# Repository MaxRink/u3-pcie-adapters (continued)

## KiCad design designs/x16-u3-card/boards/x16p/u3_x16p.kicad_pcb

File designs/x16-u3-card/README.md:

# U.3 adapter boards: x16 card, x8 card, OCuLink cage board

Passive PCIe 4.0 boards that carry true SFF-TA-1001 (U.3) wiring to 2.5" U.3 drives such as the
HPE P50230-B21 / Samsung PM1735a, which refuse U.2-wired hosts. Designed for a Jonsbo N5 build
with a 3D-printed cooling shroud.

## Boards

| Board | What it is | Status |
| --- | --- | --- |
| **x8 card** (`boards/x8/`) | x8 slot (x4x4 bifurcation), 2 drives standing upright on their connectors, connectors facing the motherboard, passive, REFCLK buffer, full sidebands, per-drive 12 V jumper and eFuse, 190 mm | rev F routed, DRC clean, all lanes ≤50 mm |
| **x16 card, passive, 4 drives** (`boards/x16p/`) | x16 slot (x4x4x4x4), 4 upright drives in a row on a 312 mm card; drives B–D sit 5.7 mm higher so lanes 8–15 pass under drive B | rev F; drive A in budget, B 45–54 mm, C ~110 mm, D ~170 mm: C/D run at PCIe Gen3 (silk says so), Gen4 on all four comes with the retimer card |
| **x16 card, passive, 3 drives** (`boards/x16p3/`) | same card with drives A–C only, 239 mm; host bifurcation x4x4x4 or x8x4x4, lanes 12–15 unused | rev F; drive C at PCIe Gen3 |
| **CDCDB400 clock versions** (`boards/*-cdcdb400/`) | the three cards above with a TI CDCDB400 instead of the PI6CB33401 / 9DBL0442 buffer | see [`docs/part-options.md`](../../docs/part-options.md) |
| **x16 card with retimer** | as above, with a retimer on lanes 8–15 so all 4 drives stay compliant | planned (part search) |
| **OCuLink cage board** (`boards/cage/`) | OCuLink 4i (SFF-8611) to U.3 breakout for a drive in a printed cage; 12 V in on a PCIe 6-pin | rev B routed, DRC clean (review fixes applied; the cabled path still needs a host-card retimer for full compliance) |

Renders are regenerated from the KiCad files whenever a board changes (see
[`tools/render`](../../tools/render/)); boards still in layout get their renders when they are DRC clean.

## OCuLink cage board

Rev B. 56.5 x 37.65 mm, 6 layers (JLC06161H-3313), PCIe lanes on L1/L6 only. The OCuLink receptacle sits on the
bottom in the edge notch, the U.3 receptacle on top mates the drive at the upper edge, and a PCIe 6-pin
(Molex Mini-Fit Jr) brings 12 V through a 3 A PTC fuse; a SOT-89 LDO (MCP1703AT-3302E/MB, pinout checked
against the Microchip datasheet; the HT7533-1 is an LCSC alternative only after its pinout is checked) makes 3.3 V aux. Four M3 slots (3.2 x 6.2 mm, along the insertion axis) hold it in
the printed cage.

Rev B changes (from the rev A review, `docs/reviews/cage-board-review.md`, and `docs/reviews/full-review-2026-11-13.md`):

- 220 nF AC caps on PER0/PER1 (bottom side, L5 voided under the pads). A U.3 drive has no TX caps on lanes 0/1
  (SFF-TA-1001 Rev 1.1 section 4.5), so rev A left those two lanes DC-coupled.
- The drive-side board edge now ends 9.4 mm from the peg line, 0.65 mm short of the housing face, so the board can
  no longer stop the drive before it is fully seated. The receptacle overhangs the edge by design.
- 100 k pull-down on PERST#: a missing or sideband-less cable holds the drive in reset.
- The four low-speed OCuLink vias moved off the PET via row into two rows in front of it, and a return via was
  added between the PET3 and PET2 transitions. The 11 mm slot in the L2/L5 planes is now two short ones with a
  2.7 mm bridge.
- Parts: F1 mSMD300-16V (3 A hold, C6851473), LED KT-0603YG (C2289), C3 50 V (C307331), LDO as above (the AMS1117
  was at its 15 V limit, needs a minimum load and is not stable with ceramic output caps).

The renders below still show rev A.

Still open on this board: the cabled path needs a retimer on the host card for full PCIe 4.0 compliance
(design-rules Rev E), PERST#/REFCLK/SMBus are not isolated when the cage is unpowered, and the PET0 lane is 30.4 mm
(0.4 mm over the per-board target).

| Top | Bottom (seen from below) |
| --- | --- |
|  |  |
|  |  |

With a 15 mm U.3 drive plugged in:

| Front | Back |
| --- | --- |
|  |  |

Copper, mask and silkscreen in the renders come from the real layer geometry. The U.3 and
OCuLink receptacles, the Mini-Fit header and the drive are simplified appearance models.

Fab files: [`fab/cage/`](fab/cage/) (Gerbers, BOM, CPL for JLCPCB / PCBWay).

## x8 card

CEM x8 edge (bifurcate the slot x4x4). Both U.3 receptacles sit on the bottom, mirrored, so the drives stand
upright with their connectors facing the motherboard and lane order needs no crossings. The card is cut away
behind the drives for airflow. A 9DBL0442 buffer (bottom side, left of the fingers) fans REFCLK out to both drives.
AC caps (220 nF) sit on the drive-to-host lanes per SFF-TA-1001. 190 mm long. Sidebands and 12 V work as described
under [Sidebands and power](#sidebands-and-power). Fab files: [`fab/x8/`](fab/x8/).

## x16 card (passive)

Same construction as the x8, four drives in a row (A–D, 73 mm pitch, 312 mm = CEM full length). The 3-drive card
(`U3_DRIVES=3 python3 gen/x16.py`) is the same design cut after drive C (239 mm). Drive B's
lane pads sit right above fingers 8–15, and right of the fingers the card edge rises to 12.75 mm, so lanes 8–15
run in a 0.9 mm-pitch stack under drive B and drives B–D sit 5.7 mm higher than A to make room. Lane lengths
finger→receptacle: A 30–46 mm, B 45–54 mm, C 107–115 mm, D 164–172 mm (the DRU documents the over-budget nets).
Drives C and D are past the Gen4 loss budget, so they are meant to run at PCIe Gen3 (silk: "C/D: PCIe Gen3 only"); the
retimer card is the Gen4 option for all four.

REFCLK (rev C): the card's 9DBL0442 (same buffer and card-level parts as the x8) feeds drive A directly and starts a
chain on L6 in the channel under drive A's block. Left of drive B a second 9DBL0442 (U40) takes the chain, drives B and
passes the clock on to a third one left of drive C (U41), which drives C and D. On the 3-drive card U40 drives B and C.
So only one clock pair ever runs under a sideband block, every pair stays short between buffers, and each repeater
gets 3.3 V aux from an extra tap on the L3 trunk. The 6-pin aux connector (J5) sits at the card end below drive D's
(or C's) power parts, with its 22 µF bulk cap on the bottom next to the +12 V pins. Fab files: [`fab/x16p/`](fab/x16p/), [`fab/x16p3/`](fab/x16p3/).

## Rev E and rev F changes (x8 and x16 cards)

**Which side the drives are on.** On these cards the receptacles are soldered to the solder side (KiCad bottom), so
the drives hang behind the card, where a CEM card may only be 2.67 mm tall and where the neighbouring slot is. This
was chosen because the U.3 lane order then matches the finger order without crossings. A version with the drives and
all tall parts on the component side is under discussion; it needs a new card-level layout and PCIe lane reversal.

Rev E (from the 2026-11-13 review):

- REFCLK buffer is the Diodes PI6CB33401ZHIEX (pin-identical to the 9DBL0442, which is the BOM alternate). Pin 1 is
  open on every buffer that runs in bypass mode.
- 4-drive card: the last repeater (U41, feeding C and D) runs as a zero-delay buffer (pin 1 to GND, low-bandwidth
  PLL) with its own ferrite and 100 nF on VDDA, so no drive sees more than two buffer delays. **This is only valid
  while drives C and D run at Gen3**, which they do on the passive card.
- TPS2116: slot 3.3 V has priority, 3.3 V aux is the fallback.
- eFuse: ITIMER 4.7 nF (about 2 ms blanking), ILIM 390 Ω (3.85 A), IMON 1 kΩ (0.25 V/A).
- x16 cards: the window edge is 9.9 mm from the receptacle peg line (rev D: 9.4). 9.4 and 9.6 do not route on the
  4-drive card. The housing face is at 10.05 mm, so only 0.15 mm is left. **Fit a drive into a bare board before
  assembling anything** and file the edge back if the drive body touches it.
  When ordering, add the note "window edges +0/-0.2 mm toward the drive": the fab's outline tolerance (about
  0.2 mm) is larger than the 0.15 mm that is left.

Rev F (all parts on the top side, 0603 or larger, or leaded):

| Feature | Where | Notes |
| --- | --- | --- |
| I2C header J6 (1x4, 2.54 mm) | bracket column | 3V3 aux, SCL, SDA, GND of the card-local bus (behind the TCA9548A) |
| EEPROM AT24C02 at 0x50 | bracket column | on the card-local bus, write-enabled |
| Test pads, 1 mm | per drive: 12 V after the eFuse, PG, IMON. Per card: 3V3 aux, 3V3, PERST#, 12 V, 12 V aux, fan tach, fan PWM | last drive's pads are labelled V, P, I |
| GND loops | bracket column and end column | for a scope ground |
| LEDs | per drive: 12 V present after the eFuse. Per card: 12 V, 12 V aux, 3V3 | the per-drive LED hangs on the drive's 12 V (2.2 k), not on PG |
| Fan header J7 (4-pin PWM) | far end of the strip | SJ4 = slot 12 V, SJ5 = aux 12 V, close exactly one. x8: slot is bridged from the fab (one via, about 1 A). x16: aux is bridged (1.0 mm on the top layer from J5, about 3 A). PWM and tach go to test pads only, so a 4-wire fan runs at full speed. **A fan above about 1 A (any 92x38 server fan) must run from aux: cut SJ4 and close SJ5 on the x8**, it does not fit the 66 W slot budget next to the drives either |
| TVS SMBJ15A | at J5 | on 12 V aux |
| M3 holes | H7–H10 in the two columns, H11 up in the strip between drives | the strip holes are searched after routing; a gap without a free spot gets none (x16: the gap between B and C on the 4-drive card) |
| Silk | bracket column | I2C address table and jumper legend |

## Sidebands and power

Every drive has its own sideband block next to its receptacle (`gen/sideband.py`), all on 3.3 V aux:

| Part | Address | Does |
| --- | --- | --- |
| TCA9543A SMBus switch | 0x70 + drive index | slot SMBus (B5/B6) to the drive's SMBus on channel 0, so drives with the same address don't collide |
| TCA9554 IO expander | 0x20 + drive index | P0 PWRDIS (10k pull-down: drive on by default), P1 DualPortEn#, P2 reset enable (pull-up), P3 locate LED, P4 PRSNT#, P5 IfDet#, P6 IfDet2#, P7 WAKE# (inputs pulled up) |
| 74LVC1G11 | | PERST0#/PERST1# = slot PERST# AND reset enable AND the drive's eFuse power-good: a drive stays in reset until its own 12 V is up, and software can hold one drive in reset |
| 74LVC1G07 | | drive WAKE# to slot WAKE# (B11), open drain, wired-OR across drives |

Card-level parts (rev C, `gen/cardkit.py`, left of the fingers):

| Part | Does |
| --- | --- |
| TCA9548A SMBus switch, 0x77 | slot SMBus to a card-local bus on channel 0, so the drive-side switches and expanders (0x70+, 0x20+) never sit on the host's segment. Close SJ1–SJ3 to move it to 0x70–0x76 if the host already uses 0x77 |
| TPS2116 power mux | card 3.3 V aux rail = slot 3.3 V (priority, rev E) or slot 3.3Vaux when main 3.3 V is off, so in S0 the card never loads 3.3Vaux |
| PI6CB33401 REFCLK buffer (9DBL0442 pinout) | slot REFCLK to every drive; its own 3.3 V through a ferrite |

HPT0 (S15) is tied to GND for U.3 x4. REFCLK1 and port B stay open (single-port x4). CLKREQ# (B12) is tied low, so
the host always drives REFCLK (as on cards without clock power management). WAKE# from every drive reaches the slot
through its 74LVC1G07 and can also be read on its expander. SMBus, 3.3 V aux, PERST# and WAKE# run as trunks on L3,
with one tap via per drive block.

**12 V:** each drive has a 3-pin jumper (JP1–JP4). Shunt on pins 2–3 (default) = slot 12 V, pins 1–2 = the PCIe
6-pin (J5). One shunt can never join the two supplies. L4 is split into a slot-12 V plane next to the fingers and an
aux-12 V plane fed only by J5. A slot gives at most 66 W at 12 V, so with more than two 25 W drives move some jumpers
to aux and plug in the 6-pin. Jumper shunts (2.54 mm) are not in the BOM. After the jumper each drive has a
TPS25982 eFuse (3.85 A circuit breaker with about 2 ms blanking, soft start, latch-off on a fault) feeding the drive's 12 V pins and bulk
caps; its power-good holds that drive's PERST#.

**Rules beyond the shared design rules (in each board's DRU):**
- Sideband blocks route at 0.127 mm tracks and 0.15 mm clearance (fab minimum 0.1 / 0.1).
- x16: REFCLK repeater links (REFCLK_R*, B, C, D) may have up to 12 mm uncoupled length (two via fans, two QFN pin
  fan-outs and the skew bumps for the turns); the other REFCLK pairs keep 8 mm.
- The eFuse's 0.5 mm-pitch QFN pins fan out at 0.2 mm on the 12 V nets inside the EFUSE rule areas; the pours carry the current.
- The slot REFCLK input may run up to 16 mm uncoupled (P/N swap at the buffer plus its deskew bumps). REFCLK is 100 MHz, so this costs no margin.
- The card's resistor array is RN10, so it does not clash with the drive blocks' RN1–RN4.

## Cooling

The drives sit in a row along the card, so the shroud's air passes them one after the other and
the last one runs hottest. Summary from [`docs/thermal`](../../docs/thermal/) (25 W per drive, 35 °C
air in, 70 °C case limit, 5 mm between drive and shroud wall):

- **x8, 2 drives:** ~20 CFM. A 92x38 mm server-class fan (~150 Pa) gives ~29 CFM and ~66 °C.
- **x16, 4 drives:** ~30 CFM at ~150 Pa. A 92x38 server fan only reaches ~28 CFM, so ~71 °C:
  marginal. 3 mm gaps (~68 °C) or a 20 W drive power state (~64 °C) give margin.
- 92x25 mm fans don't have the pressure for either card. Close the 3 mm slots between the drives
  in the shroud; they only hold stagnant air.

| CFD, 2 drives in line | CFD, 4 drives in line |
| --- | --- |
|  |  |

## Renders: x8 and x16 cards

Rendered from the routed boards in `boards/x8/` and `boards/x16p/` (PR #8), with 15 mm drives plugged in.

| x8 card | x16 card (passive) |
| --- | --- |
|  |  |
|  |  |
|  |  |
|  |  |

## Generator

All boards are generated by Python scripts on KiCad 7 `pcbnew`. To change a board, edit its script and rerun it; don't hand-edit the board.

- `lib/`: custom footprints (Amphenol PSAS4F213002 U.3 receptacle, Amphenol G14A421211112HR OCuLink 4i) and symbols
- `gen/pcbkit.py`: layout toolkit (pair router with skew bumps, zones, rule areas, DRC)
- `gen/x8.py`: x8 card (2 upright drives on the bottom, REFCLK fan-out buffer, drive window for airflow)
- `gen/x16.py`: x16 passive card (4 drives; `U3_DRIVES=3` for the 3-drive card)
- `gen/sideband.py`: per-drive sideband block (SMBus switch, IO expander, PERST# and WAKE# gates, 12 V jumper, eFuse)
- `gen/cardkit.py`: card-level parts shared by the x8 and x16 cards (REFCLK buffer, SMBus switch, 3.3 V aux OR, trunks)
- `gen/extras.py`: rev F additions (headers, test pads, LEDs, fan header, holes); runs after the block routing
- Switches: `U3_DRIVES=3|4`, `U3_CLK=cdcdb400` (alternate clock buffer, own `boards/*-cdcdb400` folder), `STAGE=card` (quick build without block routing)
- `gen/router.py`: grid maze router for the low-speed sideband nets, with rip-up and reroute and a connectivity check at the end
- `gen/cage.py`: Design 3, the OCuLink 4i to U.3 cage board (rev B, DRC clean)
- `gen/fab.py`: Gerbers, drill, BOM and CPL (JLCPCB/PCBWay)
- `boards/<board>/`: generated KiCad project, DRC report, per-net lengths
- `fab/<board>/`: Gerber zip, BOM and CPL for ordering
- `docs/ref/`: vendor drawings and third-party licences

Rules come from `../../design-rules/` (copied into each board at generation time).

Run: `python3 gen/fplib.py && python3 gen/symlib.py && python3 gen/cage.py && python3 gen/fab.py boards/cage/u3_cage.kicad_pcb boards/cage/bom_raw.json fab/cage`

Render: `xvfb-run -a python3 ../../tools/render/render.py boards/cage/u3_cage.kicad_pcb ../../docs/img/x16-u3-card --prefix cage --drives`

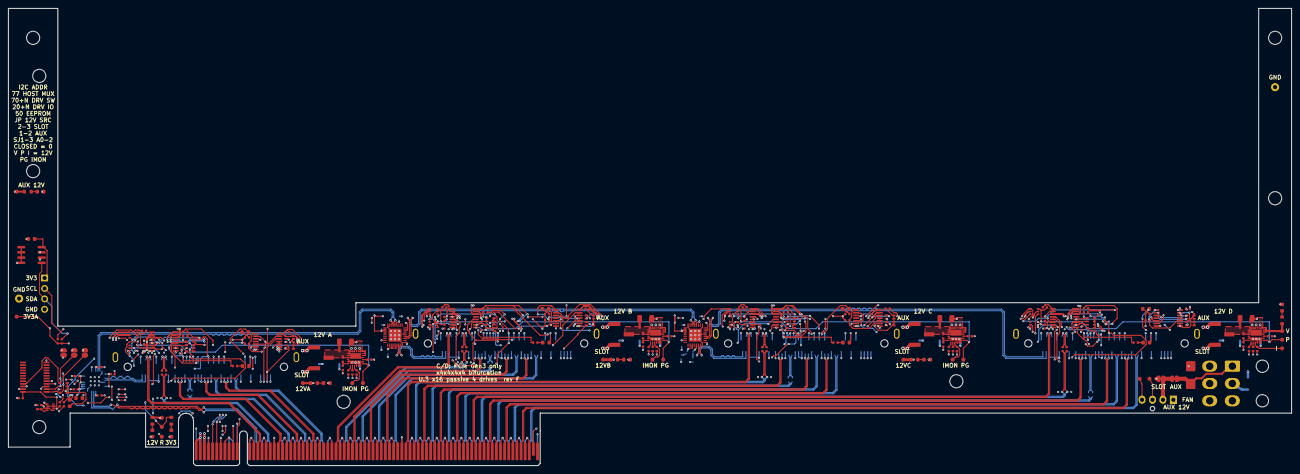
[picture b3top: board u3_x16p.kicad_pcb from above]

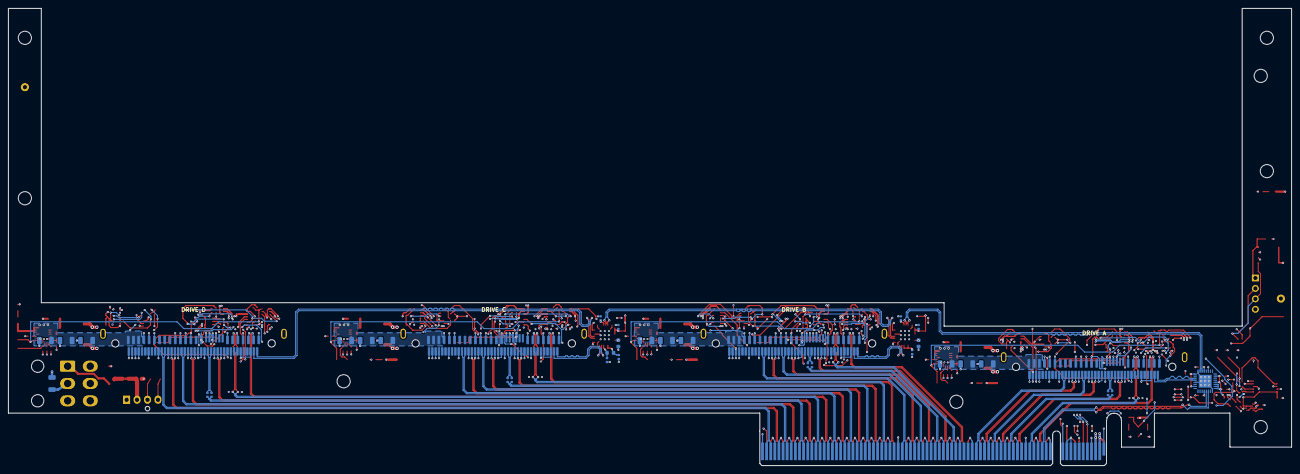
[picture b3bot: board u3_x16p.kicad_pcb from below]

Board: 6 copper layers, 312.0 x 111.2 mm, 230 parts (36 on the bottom side), 224 nets.

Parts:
C1, C2, C3, C4, C5, C6, C7, C8, C20, C21, C22, C23, C30, C31, C32, C33, C40, C41, C42, C43, C50, C51, C52, C53, C60, C62, C63, C64, C66, C67, C68: 100nF; C_0402_1005Metric
C9, C61, C65: 10uF; C_0603_1608Metric
C19, C24, C25, C34, C35, C44, C45, C54, C55: 22uF 25V X5R; C_1206_3216Metric
C26, C28, C36, C38, C46, C48, C56, C58: 10uF 50V X5R; C_1206_3216Metric
C27, C37, C47, C57: 1nF; C_0402_1005Metric
C29, C39, C49, C59: 4.7nF; C_0402_1005Metric
C90: 100nF; C_0603_1608Metric
C101, C102, C103, C104, C105, C106, C107, C108, C109, C110, C111, C112, C113, C114, C115, C116: 220nF 16V X7R; C_0402_1005Metric
D1, D2, D3, D4, D40, D41, D42, D43, D44, D45, D46: KT-0603YG; LED_0603_1608Metric
D10, D11, D12, D13: XL-1608UYC-06 yellow (locate); LED_0603_1608Metric
D50: SMBJ15A; D_SMB
FB1, FB41: 600R@100MHz; L_0603_1608Metric
H1, H2: bracket; MountingHole_3.2mm_M3
H3, H4, H5, H6: M3 slot; MountingSlot_M3_3.2x6.2
H7, H8, H9, H10, H11, H13: M3; MountingHole_3.2mm_M3
J1: PCIe x16 edge; BUS_PCIexpress_x16
J5: PCIe 6-pin 45558-0003; Molex_Mini-Fit_Jr_5569-06A2_2x03_P4.20mm_Horizontal
J6: I2C local bus; PinHeader_1x04_P2.54mm_Vertical
J7: fan 4-pin PWM; FanPinHeader_1x04_P2.54mm_Vertical
JA: PSAS4F2130021TR; Amphenol_PSAS4F213002_SFF-8639_U3_RA_SMD
JB: PSAS4F2130021TR; Amphenol_PSAS4F213002_SFF-8639_U3_RA_SMD
JC: PSAS4F2130021TR; Amphenol_PSAS4F213002_SFF-8639_U3_RA_SMD
JD: PSAS4F2130021TR; Amphenol_PSAS4F213002_SFF-8639_U3_RA_SMD
JP1, JP2, JP3, JP4: 12V src: 2-3 SLOT (default), 1-2 AUX; PinHeader_1x03_P2.54mm_Vertical_SMD_Pin1Left
R1, R2: 4.7k; R_0402_1005Metric
R3, R26, R46, R66, R86: 15k; R_0402_1005Metric
R4, R20, R21, R22, R23, R40, R41, R42, R43, R60, R61, R62, R63, R80, R81, R82, R83: 10k; R_0402_1005Metric
R11, R12, R13, R14, R24, R28, R44, R48, R64, R68, R84, R88: 1k; R_0402_1005Metric
R25, R45, R65, R85: 100k; R_0402_1005Metric
R27, R47, R67, R87: 390R; R_0402_1005Metric
R90, R91, R93, R94, R95, R96: 2.2k; R_0603_1608Metric
R92: 1k; R_0603_1608Metric
RN1, RN3, RN5, RN7: 4.7k x4; R_Array_Convex_4x0603
RN2, RN4, RN6, RN8, RN10: 10k x4; R_Array_Convex_4x0603
SJ1: A0 (close = 0); SolderJumper-2_P1.3mm_Open_RoundedPad1.0x1.5mm
SJ2: A1 (close = 0); SolderJumper-2_P1.3mm_Open_RoundedPad1.0x1.5mm
SJ3: A2 (close = 0); SolderJumper-2_P1.3mm_Open_RoundedPad1.0x1.5mm
SJ4: fan = slot 12V; SolderJumper-2_P1.3mm_Open_RoundedPad1.0x1.5mm
SJ5: fan = aux 12V (default); SolderJumper-2_P1.3mm_Bridged_RoundedPad1.0x1.5mm
TP1: 3V3_AUX; TestPoint_Pad_D1.0mm
TP2: 12V_AUX; TestPoint_Pad_D1.0mm
TP3: 12V; TestPoint_Pad_D1.0mm
TP4: 3V3; TestPoint_Pad_D1.0mm
TP5: PCIE_RST_N; TestPoint_Pad_D1.0mm
TP6: 12V_DRV_A; TestPoint_Pad_D1.0mm
TP7: IMON_A; TestPoint_Pad_D1.0mm
TP8: PG_A; TestPoint_Pad_D1.0mm
TP9: 12V_DRV_B; TestPoint_Pad_D1.0mm
TP10: IMON_B; TestPoint_Pad_D1.0mm
TP11: PG_B; TestPoint_Pad_D1.0mm
TP12: 12V_DRV_C; TestPoint_Pad_D1.0mm
TP13: IMON_C; TestPoint_Pad_D1.0mm
TP14: PG_C; TestPoint_Pad_D1.0mm
TP15: 12V_DRV_D; TestPoint_Pad_D1.0mm
TP16: PG_D; TestPoint_Pad_D1.0mm
TP17: IMON_D; TestPoint_Pad_D1.0mm
TP18: FAN_TACH; TestPoint_Pad_D1.0mm
TP19: FAN_PWM; TestPoint_Pad_D1.0mm
TP90, TP91: GND; TestPoint_Loop_D2.50mm_Drill1.0mm
U1, U40, U41: PI6CB33401ZHIEX; VQFN-32-1EP_5x5mm_P0.5mm_EP3.15x3.15mm
U2: TCA9548APWR; TSSOP-24_4.4x7.8mm_P0.65mm
U3: TPS2116DRLR; SOT-583-8
U4: AT24C02C-SSHM-T; SOIC-8_3.9x4.9mm_P1.27mm
U10, U14, U18, U22: TCA9543APWR; TSSOP-14_4.4x5mm_P0.65mm
U11, U15, U19, U23: TCA9554PWR; TSSOP-16_4.4x5mm_P0.65mm
U12, U16, U20, U24: SN74LVC1G11DCKR; SOT-363_SC-70-6
U13, U17, U21, U25: SN74LVC1G07DCKR; SOT-353_SC-70-5
U30, U31, U32, U33: TPS259824ONRGER; TI_RGE0024M_VQFN-24_4x4mm_P0.5mm_SplitEP

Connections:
3V3: C3.2, C4.2, C5.1, C8.1, FB1.1, J1.A9, J1.A10, J1.B8, R3.2, R92.2, TP4.1, U1.9, U1.10, U1.11, U1.12, U1.15, U1.19, U1.25, U1.31, U3.3, U3.5
3V3_A: C1.1, C2.1, FB1.2, U1.4, U1.21
3V3_AUX: C6.2, C9.1, C20.2, C21.2, C22.2, C23.1, C30.2, C31.2, C32.2, C33.1, C40.2, C41.2, C42.2, C43.1, C50.2, C51.2, C52.2, C53.1, C60.1, C61.2, C62.2, C63.1, C64.1, C65.2, C66.2, C67.1, C90.2, FB41.2, J6.1, JA.E3, JB.E3, JC.E3, JD.E3, R1.1, R2.1, R11.1, R12.1, R13.1, R14.1, R21.1, R22.1, R23.1, R24.1, R41.1, R42.1, R43.1, R44.1, R61.1, R62.1, R63.1, R64.1, R81.1, R82.1, R83.1, R84.1, RN1.5, RN1.6, RN1.7, RN1.8, RN2.5, RN2.6, RN2.7, RN2.8, RN3.5, RN3.6, RN3.7, RN3.8, RN4.5, RN4.6, RN4.7, RN4.8, RN5.5, RN5.6, RN5.7, RN5.8, RN6.5, RN6.6, RN6.7, RN6.8, RN7.5, RN7.6, RN7.7, RN7.8, RN8.5, RN8.6, RN8.7, RN8.8, RN10.5, RN10.6, RN10.7, RN10.8, TP1.1, U2.24, U3.2, U3.7, U4.8, U10.14, U11.16, U12.5, U13.5, U14.1, U14.14, U15.1, U15.16, U16.5, U17.5, U18.2, U18.14, U19.2, U19.16, U20.5, U21.5, U22.1, U22.2, U22.14, U23.1, U23.2, U23.16, U24.5, U25.5, U40.4, U40.9, U40.10, U40.11, U40.12, U40.15, U40.19, U40.21, U40.25, U40.31, U41.4, U41.9, U41.10, U41.11, U41.12, U41.15, U41.19, U41.25, U41.31
3V3_AUX_SLOT: C7.1, J1.B10, U3.6
3V3_PLL: C68.2, FB41.1, U41.21
12V: J1.A2, J1.A3, J1.B1, J1.B2, J1.B3, JP1.3, JP2.3, JP3.3, JP4.3, R91.2, SJ4.1, TP3.1
12V_AUX: C19.1, D50.1, J5.1, J5.2, J5.3, JP1.1, JP2.1, JP3.1, JP4.1, R90.1, SJ5.2, TP2.1
12V_DRV_A: C24.2, C25.2, C26.2, JA.P13, JA.P14, JA.P15, R93.1, TP6.1, U30.17, U30.18, U30.19, U30.20, U30.21, U30.22, U30.23, U30.24
12V_DRV_B: C34.2, C35.2, C36.2, JB.P13, JB.P14, JB.P15, R94.1, TP9.1, U31.17, U31.18, U31.19, U31.20, U31.21, U31.22, U31.23, U31.24
12V_DRV_C: C44.2, C45.2, C46.2, JC.P13, JC.P14, JC.P15, R95.1, TP12.1, U32.17, U32.18, U32.19, U32.20, U32.21, U32.22, U32.23, U32.24
12V_DRV_D: C54.2, C55.2, C56.2, JD.P13, JD.P14, JD.P15, R96.1, TP15.1, U33.17, U33.18, U33.19, U33.20, U33.21, U33.22, U33.23, U33.24
12V_FAN: J7.2, SJ4.2, SJ5.1
12V_SEL_A: C28.1, JP1.2, R25.2, U30.1, U30.2, U30.3, U30.16, U30.25
12V_SEL_B: C38.1, JP2.2, R45.2, U31.1, U31.2, U31.3, U31.16, U31.25
12V_SEL_C: C48.1, JP3.2, R65.2, U32.1, U32.2, U32.3, U32.16, U32.25
12V_SEL_D: C58.1, JP4.2, R85.2, U33.1, U33.2, U33.3, U33.16, U33.25
A_ACT_N: D1.1, JA.P11
A_LEDA: D1.2, R11.2
B_ACT_N: D2.1, JB.P11
B_LEDA: D2.2, R12.2
C_ACT_N: D3.1, JC.P11
C_LEDA: D3.2, R13.2
C_PER0_N: C102.2, JA.S6
C_PER0_P: C101.2, JA.S5
C_PER1_N: C104.2, JA.S13
C_PER1_P: C103.2, JA.S12
C_PER4_N: C106.2, JB.S6
C_PER4_P: C105.2, JB.S5
C_PER5_N: C108.2, JB.S13
C_PER5_P: C107.2, JB.S12
C_PER8_N: C110.2, JC.S6
C_PER8_P: C109.2, JC.S5
C_PER9_N: C112.2, JC.S13
C_PER9_P: C111.2, JC.S12
C_PER12_N: C114.2, JD.S6
C_PER12_P: C113.2, JD.S5
C_PER13_N: C116.2, JD.S13
C_PER13_P: C115.2, JD.S12
DPEN_A: JA.E25, U11.5
DPEN_B: JB.E25, U15.5
DPEN_C: JC.E25, U19.5
DPEN_D: JD.E25, U23.5
DRST_A: JA.E4, JA.E5, U12.4
DRST_B: JB.E4, JB.E5, U16.4
DRST_C: JC.E4, JC.E5, U20.4
DRST_D: JD.E4, JD.E5, U24.4
DVDT_A: C27.1, U30.15
DVDT_B: C37.1, U31.15
DVDT_C: C47.1, U32.15
DVDT_D: C57.1, U33.15
D_ACT_N: D4.1, JD.P11
D_LEDA: D4.2, R14.2
EN_A: R25.1, R26.2, U30.6
EN_B: R45.1, R46.2, U31.6
EN_C: R65.1, R66.2, U32.6
EN_D: R85.1, R86.2, U33.6
FAN_PWM: J7.4, TP19.1
FAN_TACH: J7.3, TP18.1
GND: C1.2, C2.2, C3.1, C4.1, C5.2, C6.1, C7.2, C8.2, C9.2, C19.2, C20.1, C21.1, C22.1, C23.2, C24.1, C25.1, C26.1, C27.2, C28.2, C29.1, C30.1, C31.1, C32.1, C33.2, C34.1, C35.1, C36.1, C37.2, C38.2, C39.1, C40.1, C41.1, C42.1, C43.2, C44.1, C45.1, C46.1, C47.2, C48.2, C49.1, C50.1, C51.1, C52.1, C53.2, C54.1, C55.1, C56.1, C57.2, C58.2, C59.1, C60.2, C61.1, C62.1, C63.2, C64.2, C65.1, C66.1, C67.2, C68.1, C90.1, D40.1, D41.1, D42.1, D43.1, D44.1, D45.1, D46.1, D50.2, J1.A4, J1.A12, J1.A15, J1.A18, J1.A20, J1.A23, J1.A24, J1.A27, J1.A28, J1.A31, J1.A34, J1.A37, J1.A38, J1.A41, J1.A42, J1.A45, J1.A46, J1.A49, J1.A51, J1.A54, J1.A55, J1.A58, J1.A59, J1.A62, J1.A63, J1.A66, J1.A67, J1.A70, J1.A71, J1.A74, J1.A75, J1.A78, J1.A79, J1.A82, J1.B4, J1.B7, J1.B12, J1.B13, J1.B16, J1.B18, J1.B21, J1.B22, J1.B25, J1.B26, J1.B29, J1.B32, J1.B35, J1.B36, J1.B39, J1.B40, J1.B43, J1.B44, J1.B47, J1.B49, J1.B52, J1.B53, J1.B56, J1.B57, J1.B60, J1.B61, J1.B64, J1.B65, J1.B68, J1.B69, J1.B72, J1.B73, J1.B76, J1.B77, J1.B80, J5.4, J5.5, J5.6, J6.4, J7.1, JA.E9, JA.E12, JA.E15, JA.E19, JA.E22, JA.MP, JA.P5, JA.P6, JA.P12, JA.S1, JA.S4, JA.S7, JA.S8, JA.S11, JA.S14, JA.S15, JA.S16, JA.S19, JA.S22, JA.S25, JA.S28, JB.E9, JB.E12, JB.E15, JB.E19, JB.E22, JB.MP, JB.P5, JB.P6, JB.P12, JB.S1, JB.S4, JB.S7, JB.S8, JB.S11, JB.S14, JB.S15, JB.S16, JB.S19, JB.S22, JB.S25, JB.S28, JC.E9, JC.E12, JC.E15, JC.E19, JC.E22, JC.MP, JC.P5, JC.P6, JC.P12, JC.S1, JC.S4, JC.S7, JC.S8, JC.S11, JC.S14, JC.S15, JC.S16, JC.S19, JC.S22, JC.S25, JC.S28, JD.E9, JD.E12, JD.E15, JD.E19, JD.E22, JD.MP, JD.P5, JD.P6, JD.P12, JD.S1, JD.S4, JD.S7, JD.S8, JD.S11, JD.S14, JD.S15, JD.S16, JD.S19, JD.S22, JD.S25, JD.S28, R4.2, R20.1, R26.1, R27.1, R28.1, R40.1, R46.1, R47.1, R48.1, R60.1, R66.1, R67.1, R68.1, R80.1, R86.1, R87.1, R88.1, SJ1.2, SJ2.2, SJ3.2, TP90.1, TP91.1, U1.8, U1.24, U1.29, U1.33, U2.12, U3.1, U4.1, U4.2, U4.3, U4.4, U4.7, U10.1, U10.2, U10.7, U11.1, U11.2, U11.3, U11.8, U12.2, U13.3, U14.2, U14.7, U15.2, U15.3, U15.8, U16.2, U17.3, U18.1, U18.7, U19.1, U19.3, U19.8, U20.2, U21.3, U22.7, U23.3, U23.8, U24.2, U25.3, U30.4, U30.5, U30.10, U30.11, U30.12, U30.14, U30.26, U31.4, U31.5, U31.10, U31.11, U31.12, U31.14, U31.26, U32.4, U32.5, U32.10, U32.11, U32.12, U32.14, U32.26, U33.4, U33.5, U33.10, U33.11, U33.12, U33.14, U33.26, U40.8, U40.24, U40.29, U40.33, U41.1, U41.8, U41.24, U41.29, U41.33
IFDET2_A: JA.E6, RN2.2, U11.11
IFDET2_B: JB.E6, RN4.2, U15.11
IFDET2_C: JC.E6, RN6.2, U19.11
IFDET2_D: JD.E6, RN8.2, U23.11
IFDET_A: JA.P4, RN2.3, U11.10
IFDET_B: JB.P4, RN4.3, U15.10
IFDET_C: JC.P4, RN6.3, U19.10
IFDET_D: JD.P4, RN8.3, U23.10
ILIM_A: R27.2, U30.8
ILIM_B: R47.2, U31.8
ILIM_C: R67.2, U32.8
ILIM_D: R87.2, U33.8
IMON_A: R28.2, TP7.1, U30.9
IMON_B: R48.2, TP10.1, U31.9
IMON_C: R68.2, TP13.1, U32.9
IMON_D: R88.2, TP17.1, U33.9
ITIMER_A: C29.2, U30.7
ITIMER_B: C39.2, U31.7
ITIMER_C: C49.2, U32.7
ITIMER_D: C59.2, U33.7
LEDA_3V3: D42.2, R92.1
LEDA_AUX: D40.2, R90.2
LEDA_DRV_A: D43.2, R93.2
LEDA_DRV_B: D44.2, R94.2
LEDA_DRV_C: D45.2, R95.2
LEDA_DRV_D: D46.2, R96.2
LEDA_SLOT: D41.2, R91.1
LOCA_A: D10.2, R24.2
LOCA_B: D11.2, R44.2
LOCA_C: D12.2, R64.2
LOCA_D: D13.2, R84.2
LOC_A: D10.1, U11.7
LOC_B: D11.1, U15.7
LOC_C: D12.1, U19.7
LOC_D: D13.1, U23.7
MUXA0: RN10.4, SJ1.1, U2.1
MUXA1: RN10.2, SJ2.1, U2.2
MUXA2: RN10.1, SJ3.1, U2.21
MUXCTL_A: R23.2, U10.3, U10.4, U10.8
MUXCTL_B: R43.2, U14.3, U14.4, U14.8
MUXCTL_C: R63.2, U18.3, U18.4, U18.8
MUXCTL_D: R83.2, U22.3, U22.4, U22.8
MUX_RST_N: RN10.3, U2.3
PCIE_RST_N: J1.A11, TP5.1, U12.1, U16.1, U20.1, U24.1
PCIE_WAKE_N: J1.B11, U13.4, U17.4, U21.4, U25.4
PER0_N: C102.1, J1.A17
PER0_P: C101.1, J1.A16
PER1_N: C104.1, J1.A22
PER1_P: C103.1, J1.A21
PER2_N: J1.A26, JA.S21
PER2_P: J1.A25, JA.S20
PER3_N: J1.A30, JA.S27
PER3_P: J1.A29, JA.S26
PER4_N: C106.1, J1.A36
PER4_P: C105.1, J1.A35
PER5_N: C108.1, J1.A40
PER5_P: C107.1, J1.A39
PER6_N: J1.A44, JB.S21
PER6_P: J1.A43, JB.S20
PER7_N: J1.A48, JB.S27
PER7_P: J1.A47, JB.S26
PER8_N: C110.1, J1.A53
PER8_P: C109.1, J1.A52
PER9_N: C112.1, J1.A57
PER9_P: C111.1, J1.A56
PER10_N: J1.A61, JC.S21
PER10_P: J1.A60, JC.S20
PER11_N: J1.A65, JC.S27
PER11_P: J1.A64, JC.S26
PER12_N: C114.1, J1.A69
PER12_P: C113.1, J1.A68
PER13_N: C116.1, J1.A73
PER13_P: C115.1, J1.A72
PER14_N: J1.A77, JD.S21
PER14_P: J1.A76, JD.S20
PER15_N: J1.A81, JD.S27
PER15_P: J1.A80, JD.S26
PET0_N: J1.B15, JA.S3
PET0_P: J1.B14, JA.S2
PET1_N: J1.B20, JA.S10
PET1_P: J1.B19, JA.S9
PET2_N: J1.B24, JA.S18
PET2_P: J1.B23, JA.S17
PET3_N: J1.B28, JA.S24
PET3_P: J1.B27, JA.S23
PET4_N: J1.B34, JB.S3
PET4_P: J1.B33, JB.S2
PET5_N: J1.B38, JB.S10
PET5_P: J1.B37, JB.S9
PET6_N: J1.B42, JB.S18
PET6_P: J1.B41, JB.S17
PET7_N: J1.B46, JB.S24
PET7_P: J1.B45, JB.S23
PET8_N: J1.B51, JC.S3
PET8_P: J1.B50, JC.S2
PET9_N: J1.B55, JC.S10
PET9_P: J1.B54, JC.S9
PET10_N: J1.B59, JC.S18
PET10_P: J1.B58, JC.S17
PET11_N: J1.B63, JC.S24
PET11_P: J1.B62, JC.S23
PET12_N: J1.B67, JD.S3
PET12_P: J1.B66, JD.S2
PET13_N: J1.B71, JD.S10
PET13_P: J1.B70, JD.S9
PET14_N: J1.B75, JD.S18
PET14_P: J1.B74, JD.S17
PET15_N: J1.B79, JD.S24
PET15_P: J1.B78, JD.S23
PG_A: R22.2, TP8.1, U12.6, U30.13
PG_B: R42.2, TP11.1, U16.6, U31.13
PG_C: R62.2, TP14.1, U20.6, U32.13
PG_D: R82.2, TP16.1, U24.6, U33.13
PR1: R3.1, R4.1, U3.4
PRSNT_A: JA.P10, RN2.4, U11.9
PRSNT_B: JB.P10, RN4.4, U15.9
PRSNT_C: JC.P10, RN6.4, U19.9
PRSNT_D: JD.P10, RN8.4, U23.9
PRSNT_N: J1.A1, J1.B81
PWRDIS_A: JA.P3, R20.2, U11.4
PWRDIS_B: JB.P3, R40.2, U15.4
PWRDIS_C: JC.P3, R60.2, U19.4
PWRDIS_D: JD.P3, R80.2, U23.4
REFCLK_A_N: JA.E8, U1.28
REFCLK_A_P: JA.E7, U1.27
REFCLK_B_N: JB.E8, U40.23
REFCLK_B_P: JB.E7, U40.22
REFCLK_C_N: JC.E8, U41.23
REFCLK_C_P: JC.E7, U41.22
REFCLK_D_N: JD.E8, U41.28
REFCLK_D_P: JD.E7, U41.27
REFCLK_IN_N: J1.A14, U1.6
REFCLK_IN_P: J1.A13, U1.5
REFCLK_RB_N: U1.23, U40.6
REFCLK_RB_P: U1.22, U40.5
REFCLK_RC_N: U40.28, U41.6
REFCLK_RC_P: U40.27, U41.5
RSTEN_A: R21.2, U11.6, U12.3
RSTEN_B: R41.2, U15.6, U16.3
RSTEN_C: R61.2, U19.6, U20.3
RSTEN_D: R81.2, U23.6, U24.3
SC1_A: RN1.1, U10.10
SC1_B: RN3.1, U14.10
SC1_C: RN5.1, U18.10
SC1_D: RN7.1, U22.10
SD1_A: RN1.2, U10.9
SD1_B: RN3.2, U14.9
SD1_C: RN5.2, U18.9
SD1_D: RN7.2, U22.9
SMBCLK_A: JA.E23, RN1.4, U10.6
SMBCLK_B: JB.E23, RN3.4, U14.6
SMBCLK_C: JC.E23, RN5.4, U18.6
SMBCLK_D: JD.E23, RN7.4, U22.6
SMBDAT_A: JA.E24, RN1.3, U10.5
SMBDAT_B: JB.E24, RN3.3, U14.5
SMBDAT_C: JC.E24, RN5.3, U18.5
SMBDAT_D: JD.E24, RN7.3, U22.5
SMCLK: J6.2, R1.2, U2.5, U4.6, U10.12, U11.14, U14.12, U15.14, U18.12, U19.14, U22.12, U23.14
SMCLK_SLOT: J1.B5, U2.22
SMDAT: J6.3, R2.2, U2.4, U4.5, U10.13, U11.15, U14.13, U15.15, U18.13, U19.15, U22.13, U23.15
SMDAT_SLOT: J1.B6, U2.23
WAKE_A: JA.P1, RN2.1, U11.12, U13.2
WAKE_B: JB.P1, RN4.1, U15.12, U17.2
WAKE_C: JC.P1, RN6.1, U19.12, U21.2
WAKE_D: JD.P1, RN8.1, U23.12, U25.2

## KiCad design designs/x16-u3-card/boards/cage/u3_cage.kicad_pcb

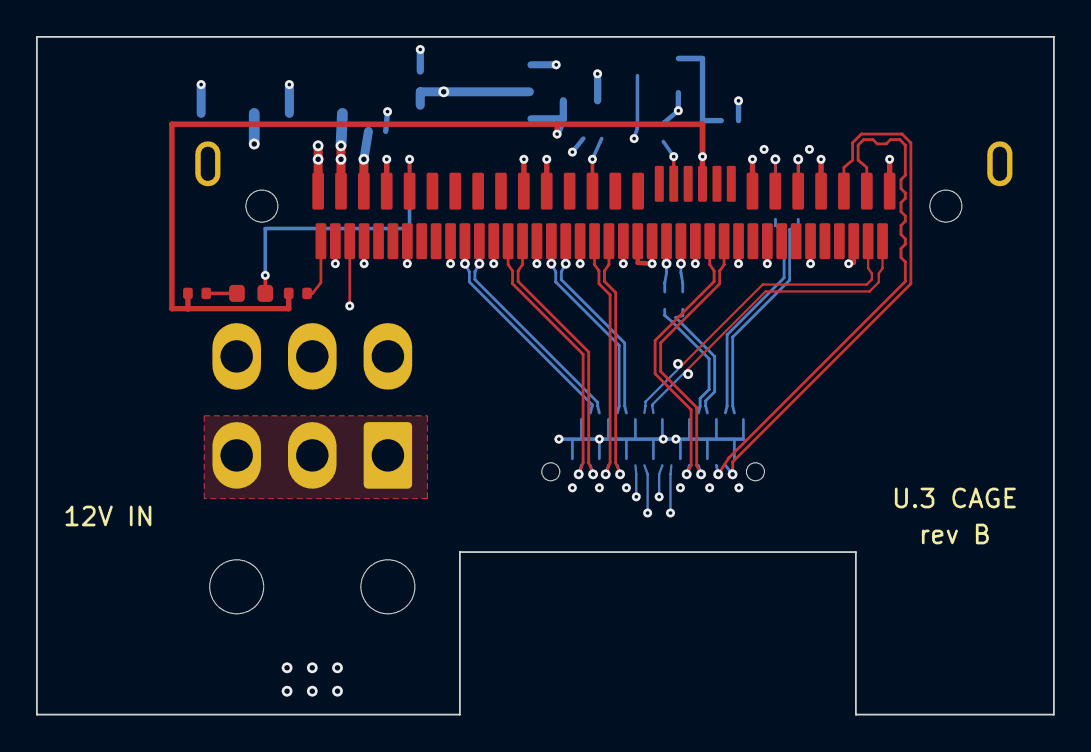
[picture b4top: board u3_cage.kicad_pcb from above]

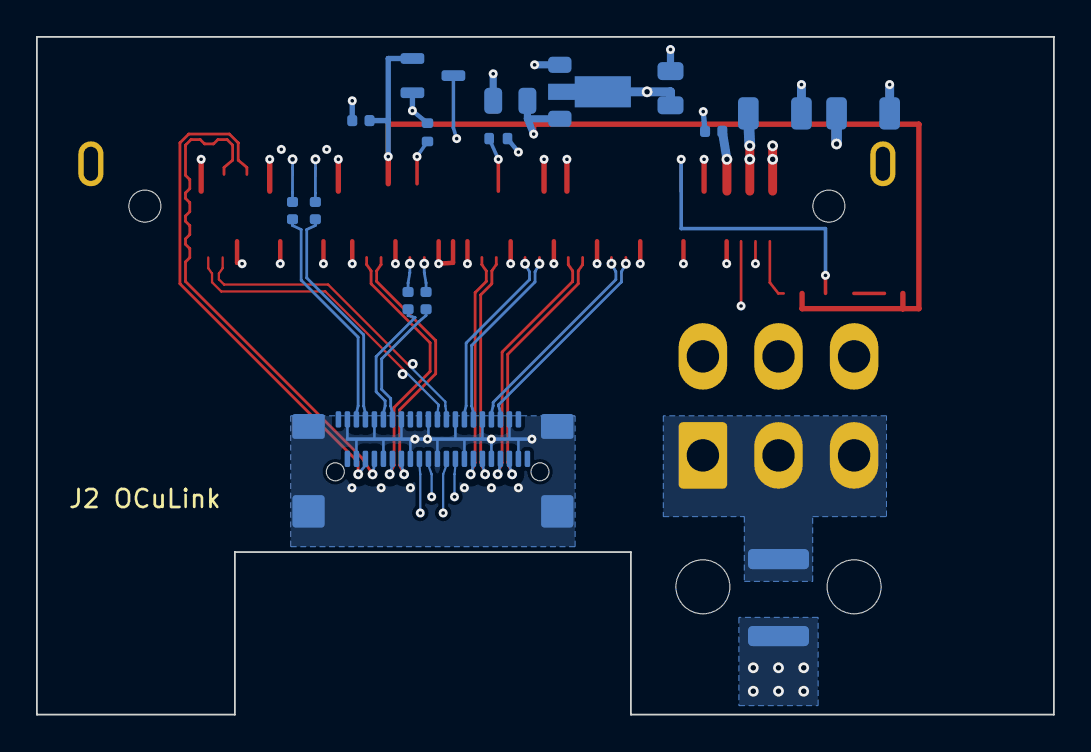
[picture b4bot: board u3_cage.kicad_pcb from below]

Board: 6 copper layers, 56.5 x 37.7 mm, 25 parts (16 on the bottom side), 34 nets.

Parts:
C1, C2: 22uF 25V X5R; C_1206_3216Metric
C3: 100nF 50V X7R; C_0402_1005Metric
C4, C5: 10uF 25V X5R; C_0805_2012Metric
C6: 100nF; C_0402_1005Metric
C11, C12, C13, C14: 220nF 16V X7R; C_0402_1005Metric
D2: KT-0603YG; LED_0603_1608Metric
F1: mSMD300-16V (3 A hold); Fuse_1812_4532Metric
H1, H2, H3, H4: M3 slot; MountingSlot_M3_3.2x6.2
J1: PSAS4F2130021TR; Amphenol_PSAS4F213002_SFF-8639_U3_RA_SMD
J2: G14A421211112HR; Amphenol_G14A421211112HR_OCuLink_4i_RA_SMD
J3: PCIe 6-pin 45558-0003; Molex_Mini-Fit_Jr_5569-06A2_2x03_P4.20mm_Horizontal
Q1: 2N7002; SOT-23-3
R3, R4: 10k; R_0402_1005Metric
R5: 1k; R_0402_1005Metric
R6: 100k; R_0402_1005Metric
U1: MCP1703AT-3302E/MB; SOT-89-3

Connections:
3V3_AUX: C5.2, C6.2, J1.E3, Q1.1, R4.1, R5.1, U1.3
12V: C1.1, C2.1, C3.2, C4.1, F1.1, J1.P13, J1.P14, J1.P15, U1.2
12V_IN: F1.2, J3.1, J3.2, J3.3
ACT_N: D2.1, J1.P11
CPRSNT_N: J2.A13, Q1.3
C_PER0_N: C12.1, J2.B3
C_PER0_P: C11.1, J2.B4
C_PER1_N: C14.1, J2.B6
C_PER1_P: C13.1, J2.B7
DUALPORTEN_N: J1.E25, R4.2
GND: C1.2, C2.2, C3.1, C4.2, C5.1, C6.1, J1.E9, J1.E12, J1.E15, J1.E19, J1.E22, J1.MP, J1.P5, J1.P6, J1.P12, J1.S1, J1.S4, J1.S7, J1.S8, J1.S11, J1.S14, J1.S15, J1.S16, J1.S19, J1.S22, J1.S25, J1.S28, J2.A2, J2.A5, J2.A8, J2.A11, J2.A14, J2.A17, J2.A20, J2.B2, J2.B5, J2.B8, J2.B11, J2.B14, J2.B17, J2.B20, J2.SH, J3.4, J3.5, J3.6, Q1.2, R3.2, R6.2, U1.1
LED_A: D2.2, R5.2
PCIE_RST_N: J1.E5, J2.A12, R6.1
PER0_N: C12.2, J1.S5
PER0_P: C11.2, J1.S6
PER1_N: C14.2, J1.S12
PER1_P: C13.2, J1.S13
PER2_N: J1.S20, J2.B15
PER2_P: J1.S21, J2.B16
PER3_N: J1.S26, J2.B18
PER3_P: J1.S27, J2.B19
PET0_N: J1.S3, J2.A3
PET0_P: J1.S2, J2.A4
PET1_N: J1.S10, J2.A7
PET1_P: J1.S9, J2.A6
PET2_N: J1.S18, J2.A16
PET2_P: J1.S17, J2.A15
PET3_N: J1.S24, J2.A19
PET3_P: J1.S23, J2.A18
PWRDIS: J1.P3, R3.1
REFCLK0_N: J1.E8, J2.B13
REFCLK0_P: J1.E7, J2.B12
SMBCLK: J1.E23, J2.A9
SMBDAT: J1.E24, J2.A10

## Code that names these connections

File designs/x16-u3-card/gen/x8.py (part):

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# 3V3_AUX (B10, L1) and PERST# (A11, L6)
VAUX = (xpin(10), -9.6); VRST = (xpin(11), -10.2)
k.track("3V3_AUX_SLOT", "L1", [(xpin(10), -5.4), VAUX], 0.3); k.via("3V3_AUX_SLOT", *VAUX)
k.track("PCIE_RST_N", "L6", [(xpin(11), -5.4), VRST], 0.2); k.via("PCIE_RST_N", *VRST)
# PRSNT1# (A1) -> PRSNT2# x8 (B48) on L3
VPA = (xpin(1), -9.0); VPB = (95.6, -8.0)
k.track("PRSNT_N", "L6", [(xpin(1), -4.6), VPA], 0.2); k.via("PRSNT_N", *VPA)
k.track("PRSNT_N", "L1", [(xpin(48), -5.4), (xpin(48), -7.3), VPB], 0.2); k.via("PRSNT_N", *VPB)
k.track("PRSNT_N", "L3", [VPA, (95.0, VPA[1]), VPB], 0.2)        # crosses the key slot above its 8.4 mm top

# activity LEDs (top side, over the receptacle): 3V3_AUX -> 1k -> LED -> ACT#
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card.clock_channel("B", 2, row=YP + sideband.CLK_Y[0], xdrop=XB - 25.0)
# slot SMBus: B5/B6 -> vias -> the TCA9548A upstream port
VSC, VSD = (xpin(5), -10.0), (xpin(6), -10.6)
k.track("SMCLK_SLOT", "L1", [(xpin(5), -5.4), VSC], 0.2); k.via("SMCLK_SLOT", *VSC)
k.track("SMDAT_SLOT", "L1", [(xpin(6), -5.4), VSD], 0.2); k.via("SMDAT_SLOT", *VSD)
first = card.trunks({"SMCLK": 13.5, "SMDAT": 14.5, "3V3_AUX": 15.5, "PCIE_RST_N": 27.45, "PCIE_WAKE_N": 28.3})
# slot PERST#/WAKE#: west on L3 under the REFCLK_IN run (clear of the CEM notch), north up the left side of drive A's
# receptacle to the trunk starts; the router only does the short hop from the finger vias
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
